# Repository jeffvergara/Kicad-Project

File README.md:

# Kicad-Project

Multiple Inputs going to Rapsberry

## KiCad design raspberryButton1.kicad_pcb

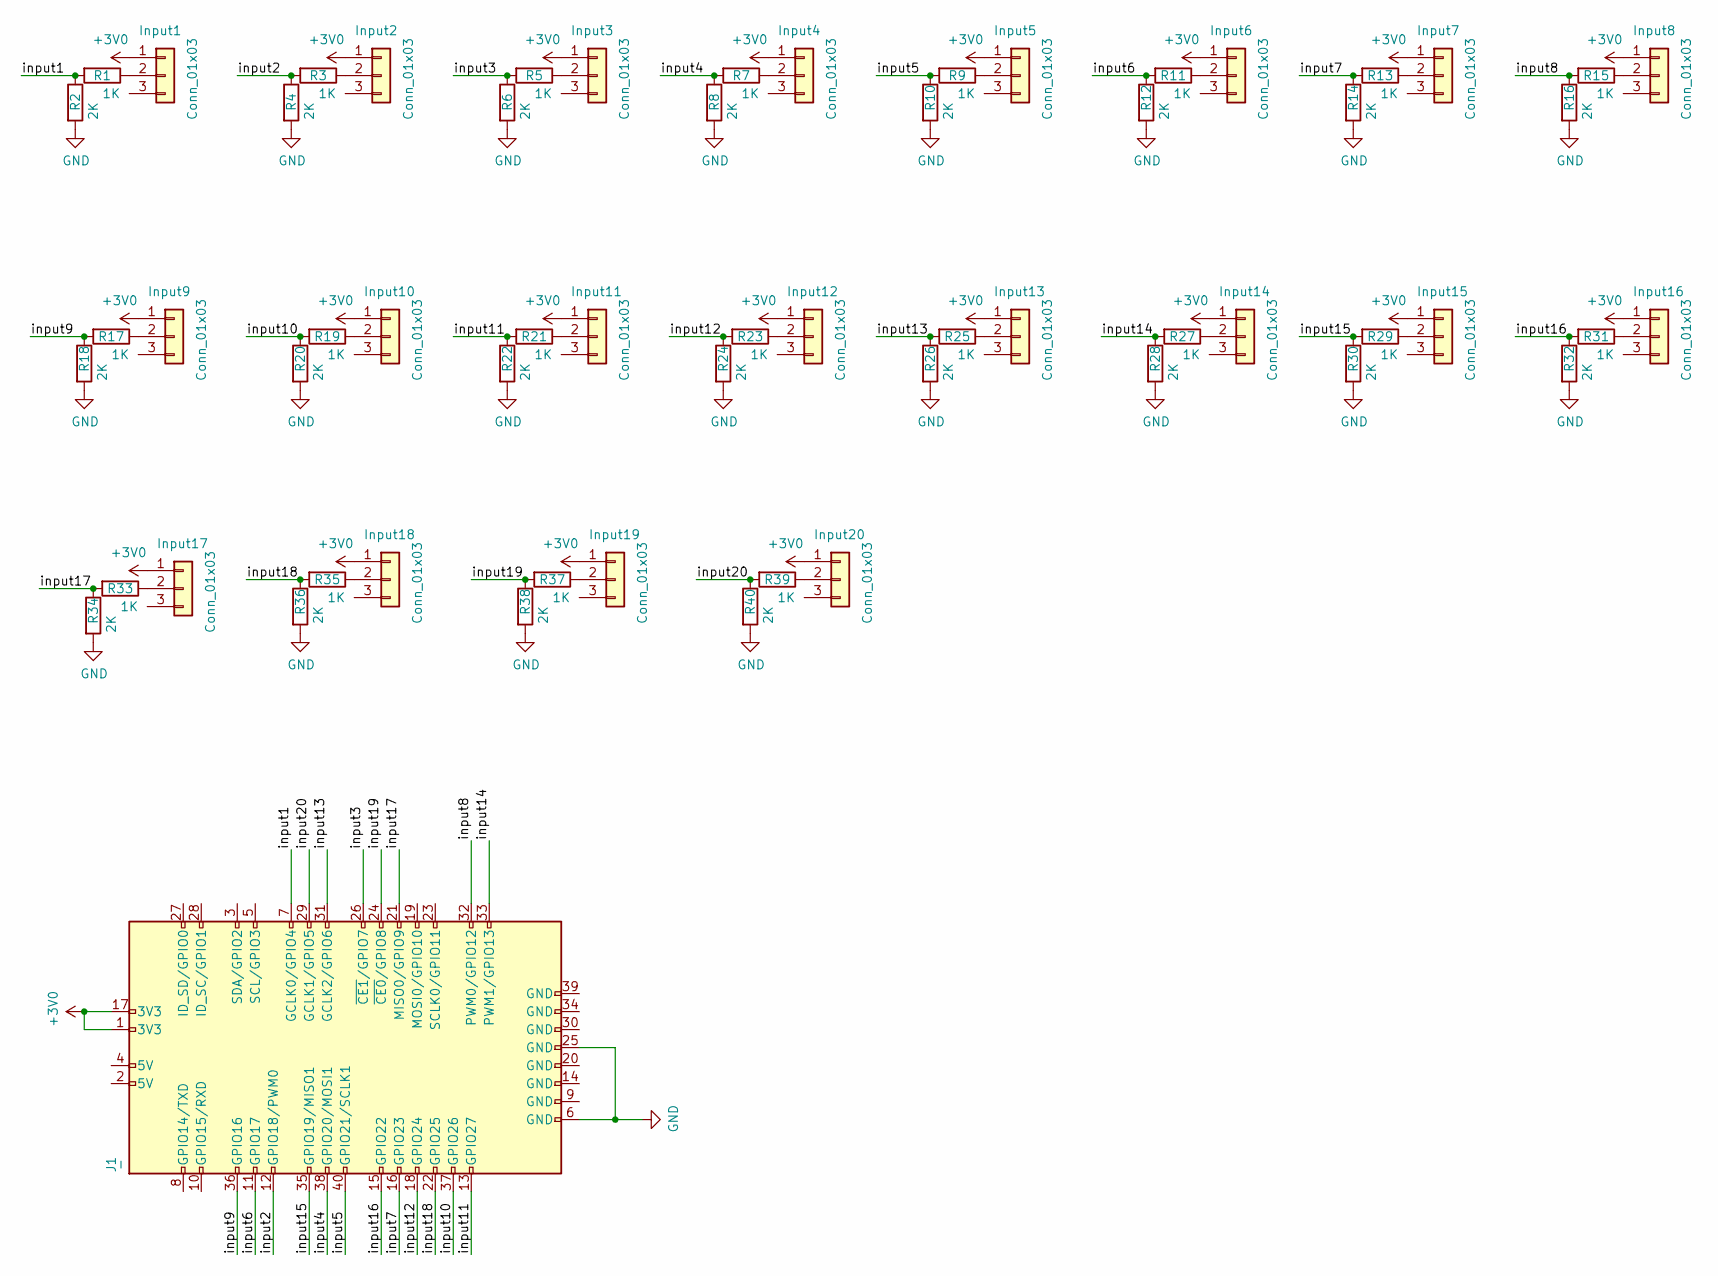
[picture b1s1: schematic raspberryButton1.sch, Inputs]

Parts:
Input1, Input2, Input3, Input4, Input5, Input6, Input7, Input8, Input9, Input10, Input11, Input12, Input13, Input14, Input15, Input16, Input17, Input18, Input19, Input20: Conn_01x03; JST_EH_B3B-EH-A_1x03_P2.50mm_Vertical
J1: -; IDC-Header_2x20_P2.54mm_Vertical
R1, R3, R5, R7, R9, R11, R13, R15, R17, R19, R21, R23, R25, R27, R29, R31, R33, R35, R37, R39: 1K; R_0201_0603Metric
R2, R4, R6, R8, R10, R12, R14, R16, R18, R20, R22, R24, R26, R28, R30, R32, R34, R36, R38, R40: 2K; R_0201_0603Metric

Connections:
+3V0: Input1.1, Input2.1, Input3.1, Input4.1, Input5.1, Input6.1, Input7.1, Input8.1, Input9.1, Input10.1, Input11.1, Input12.1, Input13.1, Input14.1, Input15.1, Input16.1, Input17.1, Input18.1, Input19.1, Input20.1, J1.1 (3V3), J1.17 (3V3)
/input1: J1.7 (GCLK0/GPIO4), R1.2, R2.1
/input2: J1.12 (GPIO18/PWM0), R3.2, R4.1
/input3: J1.26 (~CE1~/GPIO7), R5.2, R6.1
/input4: J1.38 (GPIO20/MOSI1), R7.2, R8.1
/input5: J1.40 (GPIO21/SCLK1), R9.2, R10.1
/input6: J1.11 (GPIO17), R11.2, R12.1
/input7: J1.16 (GPIO23), R13.2, R14.1
/input8: J1.32 (PWM0/GPIO12), R15.2, R16.1
/input9: J1.36 (GPIO16), R17.2, R18.1
/input10: J1.37 (GPIO26), R19.2, R20.1
/input11: J1.13 (GPIO27), R21.2, R22.1
/input12: J1.18 (GPIO24), R23.2, R24.1
/input13: J1.31 (GCLK2/GPIO6), R25.2, R26.1
/input14: J1.33 (PWM1/GPIO13), R27.2, R28.1
/input15: J1.35 (GPIO19/MISO1), R29.2, R30.1
/input16: J1.15 (GPIO22), R31.2, R32.1
/input17: J1.21 (MISO0/GPIO9), R33.2, R34.1
/input18: J1.22 (GPIO25), R35.2, R36.1
/input19: J1.24 (~CE0~/GPIO8), R37.2, R38.1
/input20: J1.29 (GCLK1/GPIO5), R39.2, R40.1
GND: J1.6 (GND), J1.25 (GND), R2.2, R4.2, R6.2, R8.2, R10.2, R12.2, R14.2, R16.2, R18.2, R20.2, R22.2, R24.2, R26.2, R28.2, R30.2, R32.2, R34.2, R36.2, R38.2, R40.2
unnamed: Input1.2, R1.1
unnamed: Input2.2, R3.1
unnamed: Input3.2, R5.1
unnamed: Input4.2, R7.1
unnamed: Input5.2, R9.1
unnamed: Input6.2, R11.1
unnamed: Input7.2, R13.1
unnamed: Input8.2, R15.1
unnamed: Input9.2, R17.1
unnamed: Input10.2, R19.1
unnamed: Input11.2, R21.1
unnamed: Input12.2, R23.1
unnamed: Input13.2, R25.1
unnamed: Input14.2, R27.1
unnamed: Input15.2, R29.1
unnamed: Input16.2, R31.1
unnamed: Input17.2, R33.1
unnamed: Input18.2, R35.1
unnamed: Input19.2, R37.1
unnamed: Input20.2, R39.1

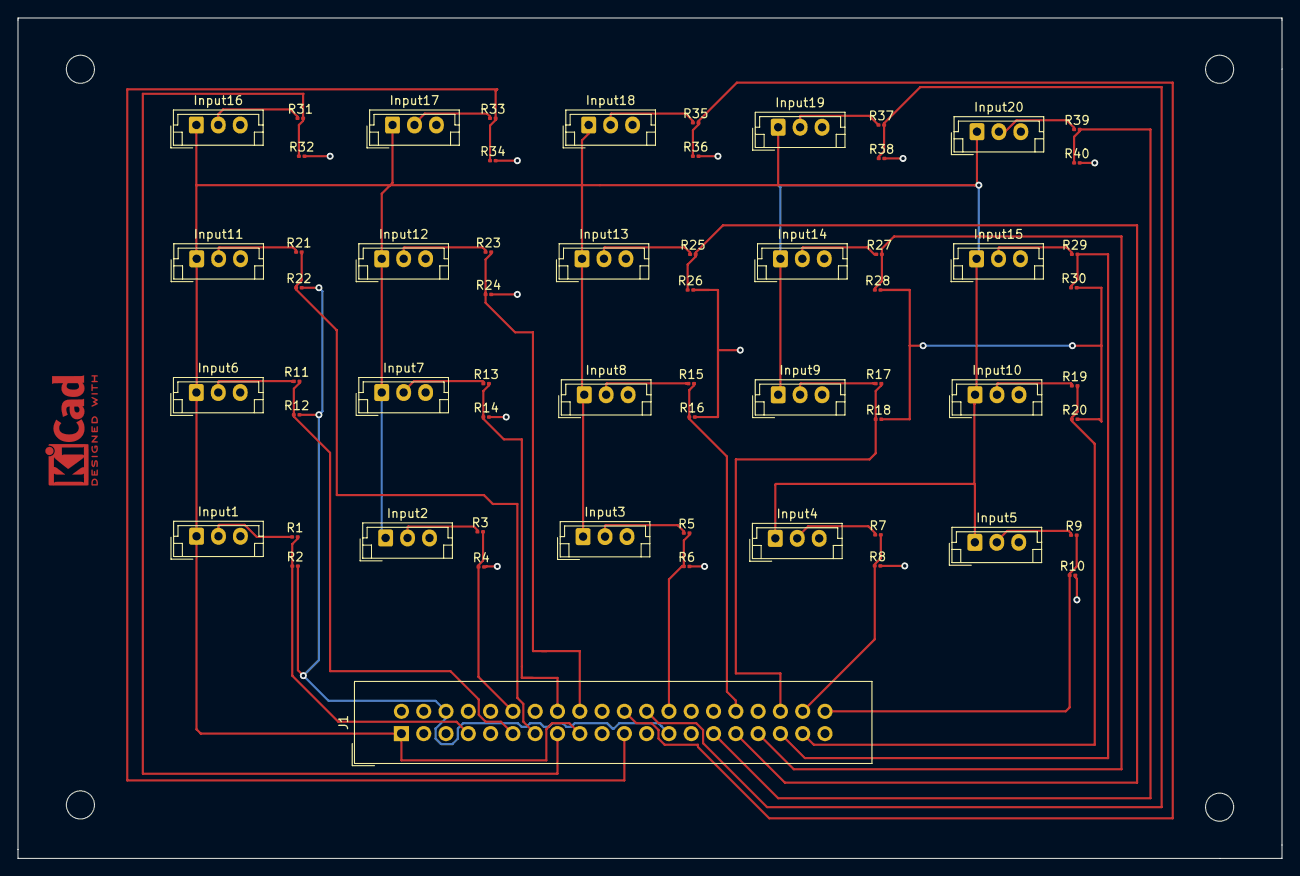
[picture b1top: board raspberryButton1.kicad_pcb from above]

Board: 2 copper layers, 144.0 x 95.8 mm, 61 parts (0 on the bottom side), 42 nets.
